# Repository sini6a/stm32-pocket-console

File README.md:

# STM32 Pocket Game/Dev Console 🕹️

The STM32 Pocket Game/Dev Console 🕹️ is a handheld device powered by 2xAAA batteries. This compact console features 5 programmable buttons, 2 LEDs, and an SPI TFT 2.4" display with a resolution of 320x240 pixels.

Originally equipped with a TagConnect connector for programming, the board underwent a redesign, now featuring a basic 2.54mm pitch connector for enhanced programming flexibility.

Measuring only 97x70mm, this board is designed to be easily customized for various purposes according to your specific needs.

## Key Features:

-   Powered by 2xAAA batteries for portability.
-   5 programmable input buttons for versatile interaction.
-   2 LEDs for status indication.
-   Battery voltage monitoring through analog readings.
-   2.4" SPI TFT display with a resolution of 320x240 pixels.
-   2.54mm pitch connector for programming convenience.

## Manufacturing:

PCBWay generously sponsored the production of this board, providing top-notch PCB manufacturing services. The boards were carefully packaged and demonstrated excellent quality. I was delighted to receive them at my destination within just a week of placing the order.

Beyond their exceptional manufacturing capabilities, PCBWay offers additional services such as PCB assembly, 3D printing, and CNC machining. These services empower you to transform your project into a comprehensive, ready-to-use product that can be easily sold or instantly put into use.

If you're interested in building this device, you can find the manufacturing files in the `/gerbers` folder. Head to [PCBWay](https://www.pcbway.com/) to get your boards manufactured.

## Programming:

This board is compatible with various STM32 programmers, including ST-Link and J-Link. I used a cheaper programmer called DAPLINK from AliExpress, as shown in the image below, for the actual programming. Make sure to check the schematics to match the exposed SWD interface with your programmer.

## Customization:

The compact size of 97x70mm allows for easy customization, making it adaptable to different use cases based on your requirements.

Feel free to explore the possibilities and unleash the potential of the STM32 Pocket Game/Dev Console for your unique projects!

### Disclaimer:

This project is still a work in progress as the software has not been officially completed, and additional tests are pending to ensure the stability and performance of the device. Stay tuned for updates, or feel free to build one yourself if you enjoy experimenting.

## Support

If you find this project useful, you can buy me a coffee:

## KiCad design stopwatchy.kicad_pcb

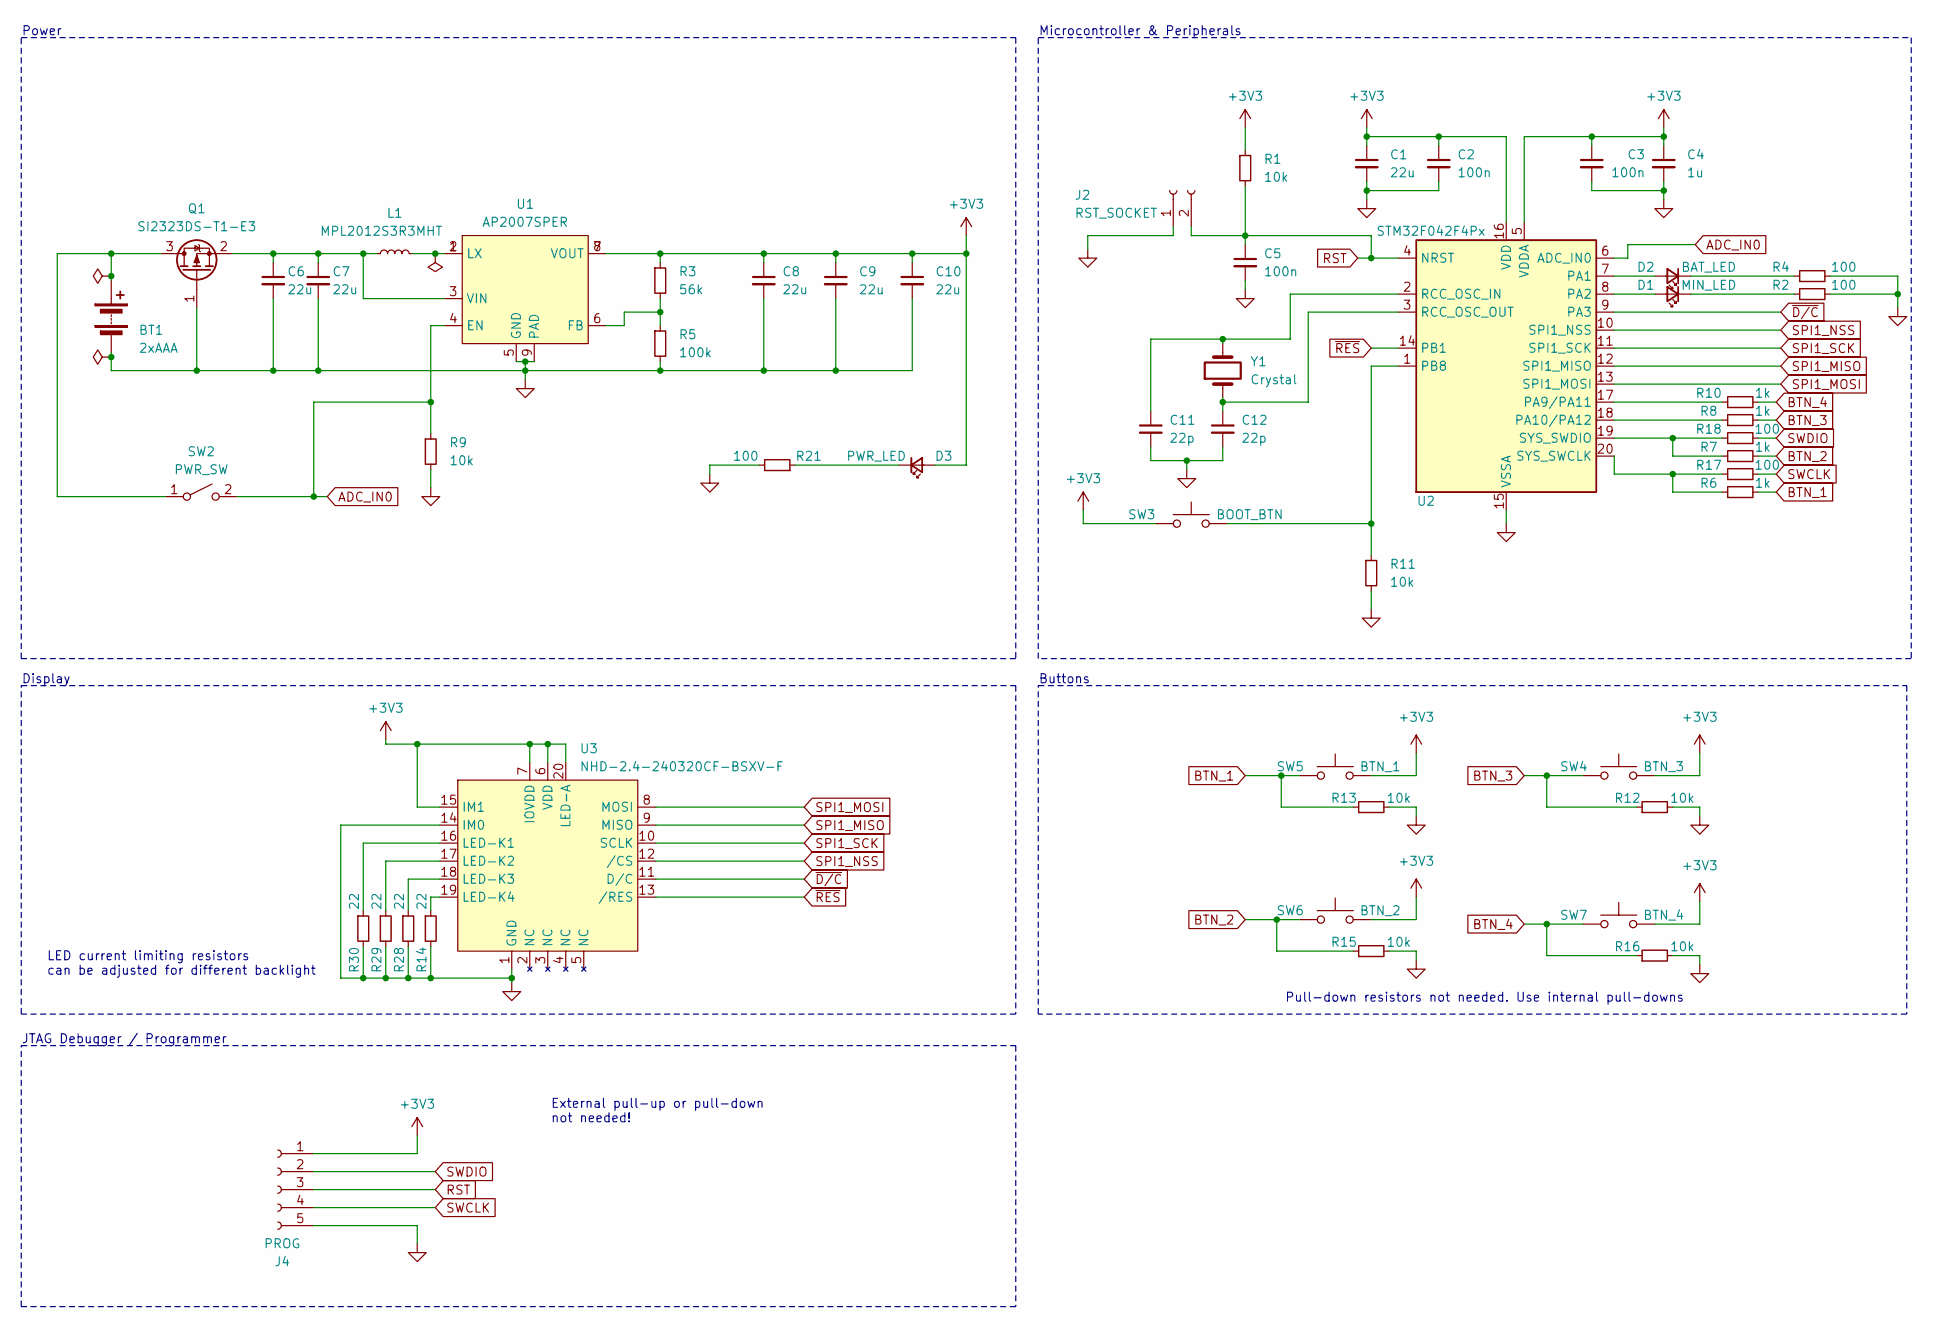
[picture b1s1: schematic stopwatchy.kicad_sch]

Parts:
BT1: 2xAAA; BH-AAA-B5AK001; LCSC C964882
C1, C6, C7, C8, C9: 22u; C_0805_2012Metric; LCSC C45783
C2, C3: 100n; C_0603_1608Metric; LCSC C14663
C4: 1u; C_0805_2012Metric; LCSC C28323
C5: 100n; C_0603_1608Metric
C10: 22u; C_0805_2012Metric
C11, C12: 22p; C_0603_1608Metric; LCSC C1653
D1: MIN_LED; LED_0805_2012Metric; LCSC C2297
D2: BAT_LED; LED_0805_2012Metric; LCSC C2296
D3: PWR_LED; LED_0805_2012Metric; LCSC C84256
J2: RST_SOCKET; TestPoint_2Pads_Pitch5.08mm_Drill1.3mm
J4: PROG; PinHeader_2x03_P2.54mm_Vertical
L1: MPL2012S3R3MHT; L_0805_2012Metric
Q1: SI2323DS-T1-E3; SOT-23; LCSC C141511
R1, R9, R11, R12, R13, R15, R16: 10k; R_0603_1608Metric; LCSC C25804
R2, R4, R17, R18, R21: 100; R_0603_1608Metric; LCSC C22775
R3: 56k; R_0603_1608Metric; LCSC C25602
R5: 100k; R_0603_1608Metric; LCSC C25803
R6, R7, R8, R10: 1k; R_0603_1608Metric; LCSC C21190
R14, R28, R29, R30: 22; R_0603_1608Metric; LCSC C22775
SW2: PWR_SW; SW_CuK_OS102011MA1QN1_SPDT_Angled; LCSC C2681575
SW3: BOOT_BTN; SW_PUSH_6mm
SW4: BTN_3; SW_PUSH_6mm
SW5: BTN_1; SW_PUSH_6mm
SW6: BTN_2; SW_PUSH_6mm
SW7: BTN_4; SW_PUSH_6mm
U1: AP2007SPER; SOIC-8-1EP_3.9x4.9mm_P1.27mm_EP2.41x3.3mm; LCSC C130338
U2: STM32F042F4Px; TSSOP-20_4.4x6.5mm_P0.65mm; LCSC C81002
U3: NHD-2.4-240320CF-BSXV-F
Y1: Crystal; Crystal_SMD_HC49-SD

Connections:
+3V3: C1.1, C2.1, C3.1, C4.1, C8.1, C9.1, C10.1, D3.2 (A), J4.1, R1.1, R3.1, SW3.1, SW4.2, SW5.2, SW6.2, SW7.2, U1.7 (VOUT), U1.8 (VOUT), U2.5 (VDDA), U2.16 (VDD), U3.6 (VDD), U3.7 (IOVDD), U3.15 (IM1), U3.20 (LED-A)
ADC_IN0: R9.1, SW2.2 (B), U1.4 (EN), U2.6 (ADC_IN0)
BTN_1: R6.2, R13.1, SW5.1
BTN_2: R7.2, R15.1, SW6.1
BTN_3: R8.2, R12.1, SW4.1
BTN_4: R10.2, R16.1, SW7.1
GND: BT1.2 (-), C1.2, C2.2, C3.2, C4.2, C5.2, C6.2, C7.2, C8.2, C9.2, C10.2, C11.2, C12.2, J2.1, J4.5, Q1.1 (G), R2.2, R4.2, R5.2, R9.2, R11.2, R12.2, R13.2, R14.2, R15.2, R16.2, R21.2, R28.2, R29.2, R30.2, U1.5 (GND), U1.9 (PAD), U2.15 (VSSA), U3.1 (GND), U3.14 (IM0)
unnamed: BT1.1 (+), Q1.3 (D), SW2.1 (A)
unnamed: D1.2 (A), U2.8 (PA2)
unnamed: D1.1 (K), R2.1
unnamed: D2.2 (A), U2.7 (PA1)
unnamed: D2.1 (K), R4.1
unnamed: D3.1 (K), R21.1
unnamed: L1.2, U1.1 (LX), U1.2 (LX)
unnamed: C6.1, C7.1, L1.1, Q1.2 (S), U1.3 (VIN)
unnamed: R3.2, R5.1, U1.6 (FB)
unnamed: R10.1, U2.17 (PA9/PA11)
unnamed: R8.1, U2.18 (PA10/PA12)
unnamed: R7.1, R18.1, U2.19 (SYS_SWDIO)
unnamed: R6.1, R17.1, U2.20 (SYS_SWCLK)
unnamed: R11.1, SW3.2, U2.1 (PB8)
unnamed: C11.1, U2.2 (RCC_OSC_IN), Y1.2
unnamed: C12.1, U2.3 (RCC_OSC_OUT), Y1.1
unnamed: R30.1, U3.16 (LED-K1)
unnamed: R29.1, U3.17 (LED-K2)
unnamed: R28.1, U3.18 (LED-K3)
unnamed: R14.1, U3.19 (LED-K4)
RST: C5.1, J2.2, J4.3, R1.2, U2.4 (NRST)
SPI1_MISO: U2.12 (SPI1_MISO), U3.9 (MISO)
SPI1_MOSI: U2.13 (SPI1_MOSI), U3.8 (MOSI)
SPI1_NSS: U2.10 (SPI1_NSS), U3.12 (/CS)
SPI1_SCK: U2.11 (SPI1_SCK), U3.10 (SCLK)
SWCLK: J4.4, R17.2
SWDIO: J4.2, R18.2
~D/C: U2.9 (PA3), U3.11 (D/C)
~RES: U2.14 (PB1), U3.13 (/RES)

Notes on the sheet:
Display
External pull-up or pull-down not needed!
LED current limiting resistors can be adjusted for different backlight
Microcontroller & Peripherals
Pull-down resistors not needed. Use internal pull-downs
Power
Buttons
JTAG Debugger / Programmer

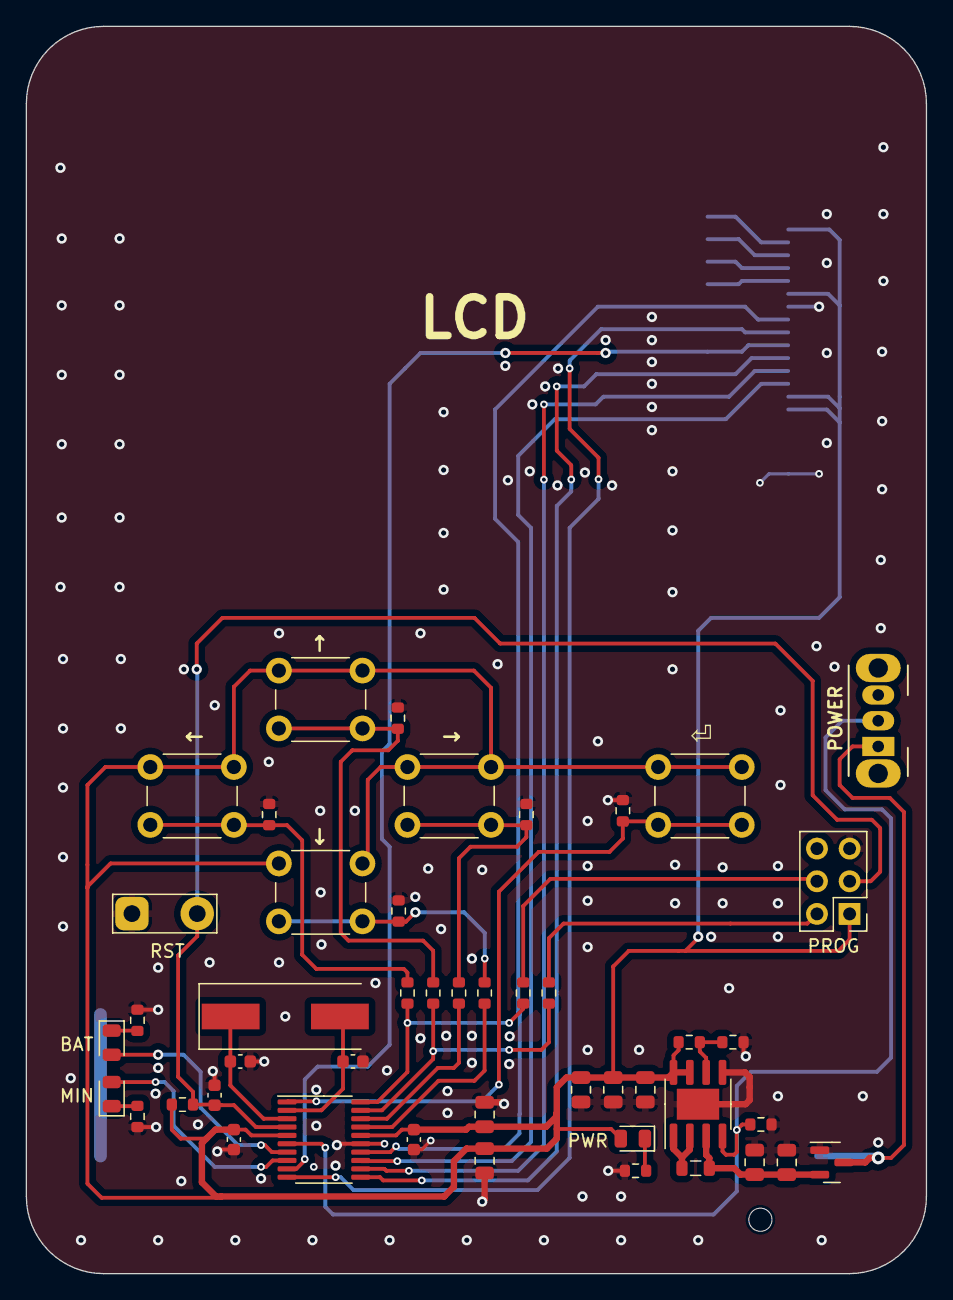
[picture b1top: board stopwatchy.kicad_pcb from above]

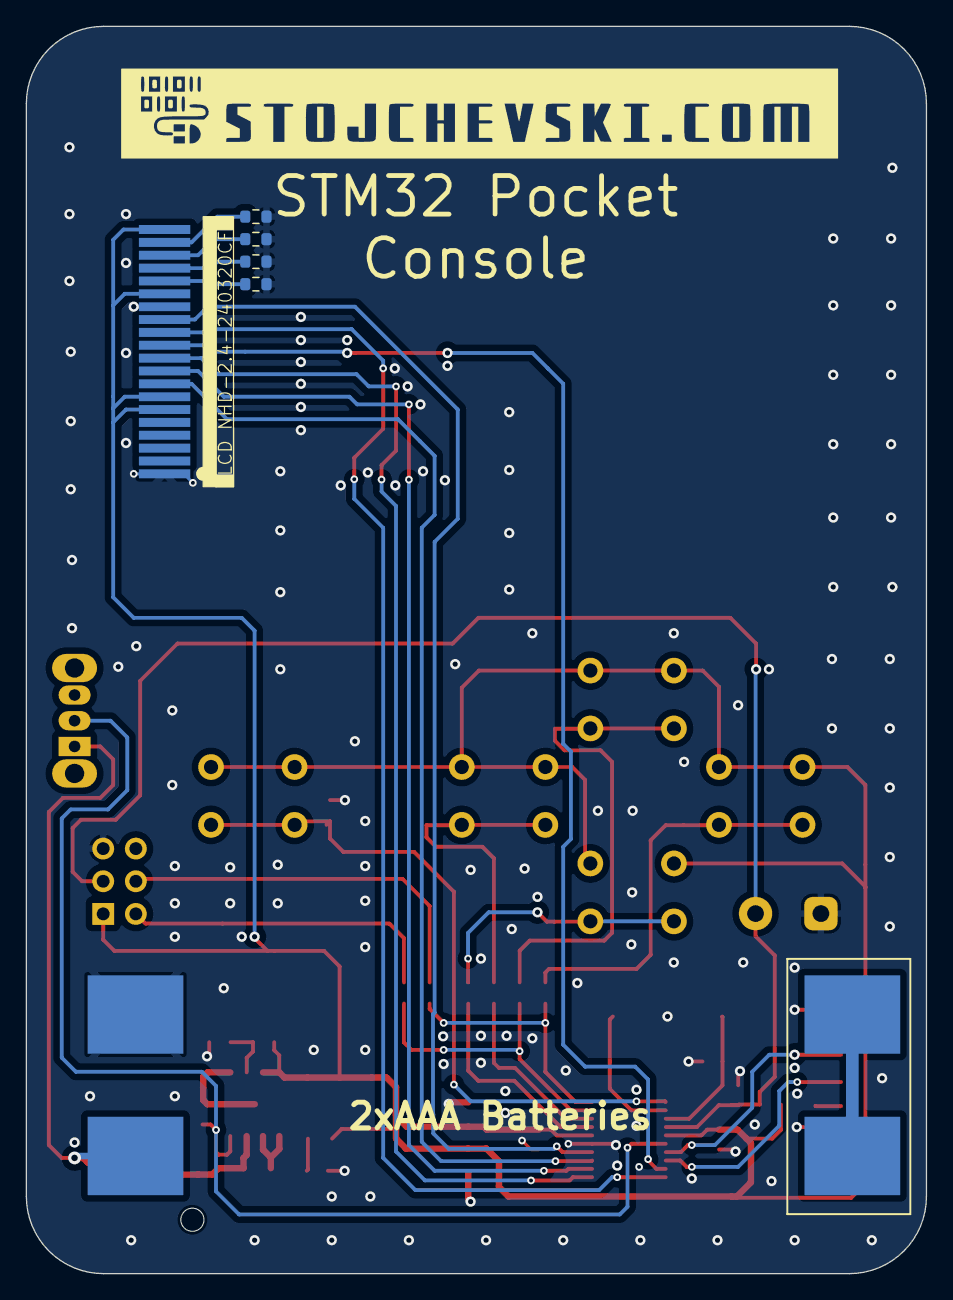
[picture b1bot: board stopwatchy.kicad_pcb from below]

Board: 2 copper layers, 70.0 x 97.0 mm, 52 parts (6 on the bottom side), 36 nets.

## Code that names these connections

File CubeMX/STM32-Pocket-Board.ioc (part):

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Mcu.Name=STM32F042F4Px
Mcu.Package=TSSOP20
Mcu.UserName=STM32F042F4Px
PA0.Mode=IN0
PA0.Signal=ADC_IN0
PA1.GPIOParameters=GPIO_Label
PA1.GPIO_Label=BAT_LED
PA1.Signal=GPIO_Output
PA10.GPIOParameters=GPIO_PuPd
PA10.GPIO_PuPd=GPIO_PULLDOWN
PA10.Signal=GPIO_Input
PA13.GPIOParameters=GPIO_PuPd
PA13.GPIO_PuPd=GPIO_PULLDOWN
PA13.Signal=GPIO_Input
PA14.GPIOParameters=GPIO_PuPd
PA14.GPIO_PuPd=GPIO_PULLDOWN
PA14.Signal=GPIO_Input
PA2.GPIOParameters=GPIO_Label
PA2.GPIO_Label=MIN_LED
PA2.Signal=GPIO_Output
PA3.Signal=GPIO_Analog
PA5.Mode=Full_Duplex_Master
PA5.Signal=SPI1_SCK
PA6.Mode=Full_Duplex_Master
PA6.Signal=SPI1_MISO
PA7.Mode=Full_Duplex_Master
PA7.Signal=SPI1_MOSI
PA9.GPIOParameters=GPIO_PuPd
PA9.GPIO_PuPd=GPIO_PULLDOWN
PA9.Signal=GPIO_Input
PB8.GPIOParameters=GPIO_PuPd
PB8.GPIO_PuPd=GPIO_PULLDOWN
PB8.Signal=GPIO_Input
PF0-OSC_IN.Mode=HSE-External-Oscillator
PF0-OSC_IN.Signal=RCC_OSC_IN
PF1-OSC_OUT.Mode=HSE-External-Oscillator
PF1-OSC_OUT.Signal=RCC_OSC_OUT
RCC.HSE_VALUE=16000000
RCC.SYSCLKFreq_VALUE=32000000
RCC.SYSCLKSource=RCC_SYSCLKSOURCE_PLLCLK
board=custom

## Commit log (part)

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2024-03-05 minor improvements in 3d models
2024-03-05 added schematics
2024-03-05 readme + updated images
2024-03-05 added icon
2024-03-05 added icon again
2024-03-05 disclaimer
2024-03-11 initial firmware
2024-03-13 updated to ext clock and connected all buttons
2024-03-13 updated ioc to match the project
2024-03-13 updated to match ioc
2024-03-23 updated readme with finished project
2024-03-23 updated adc_in route from switch and changed R1 from 560k to 56k
2024-03-23 updated pocket console image
2024-03-23 deleted image
2024-03-23 reuploaded image
2024-03-23 removed unneeded resistors, fixed lcd connector placement, removed vias
